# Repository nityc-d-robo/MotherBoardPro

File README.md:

This project needs some libraries in nityc-d-robo/d_robo_lib . So first, import them to Kicad5 and then, open this circuit datas.

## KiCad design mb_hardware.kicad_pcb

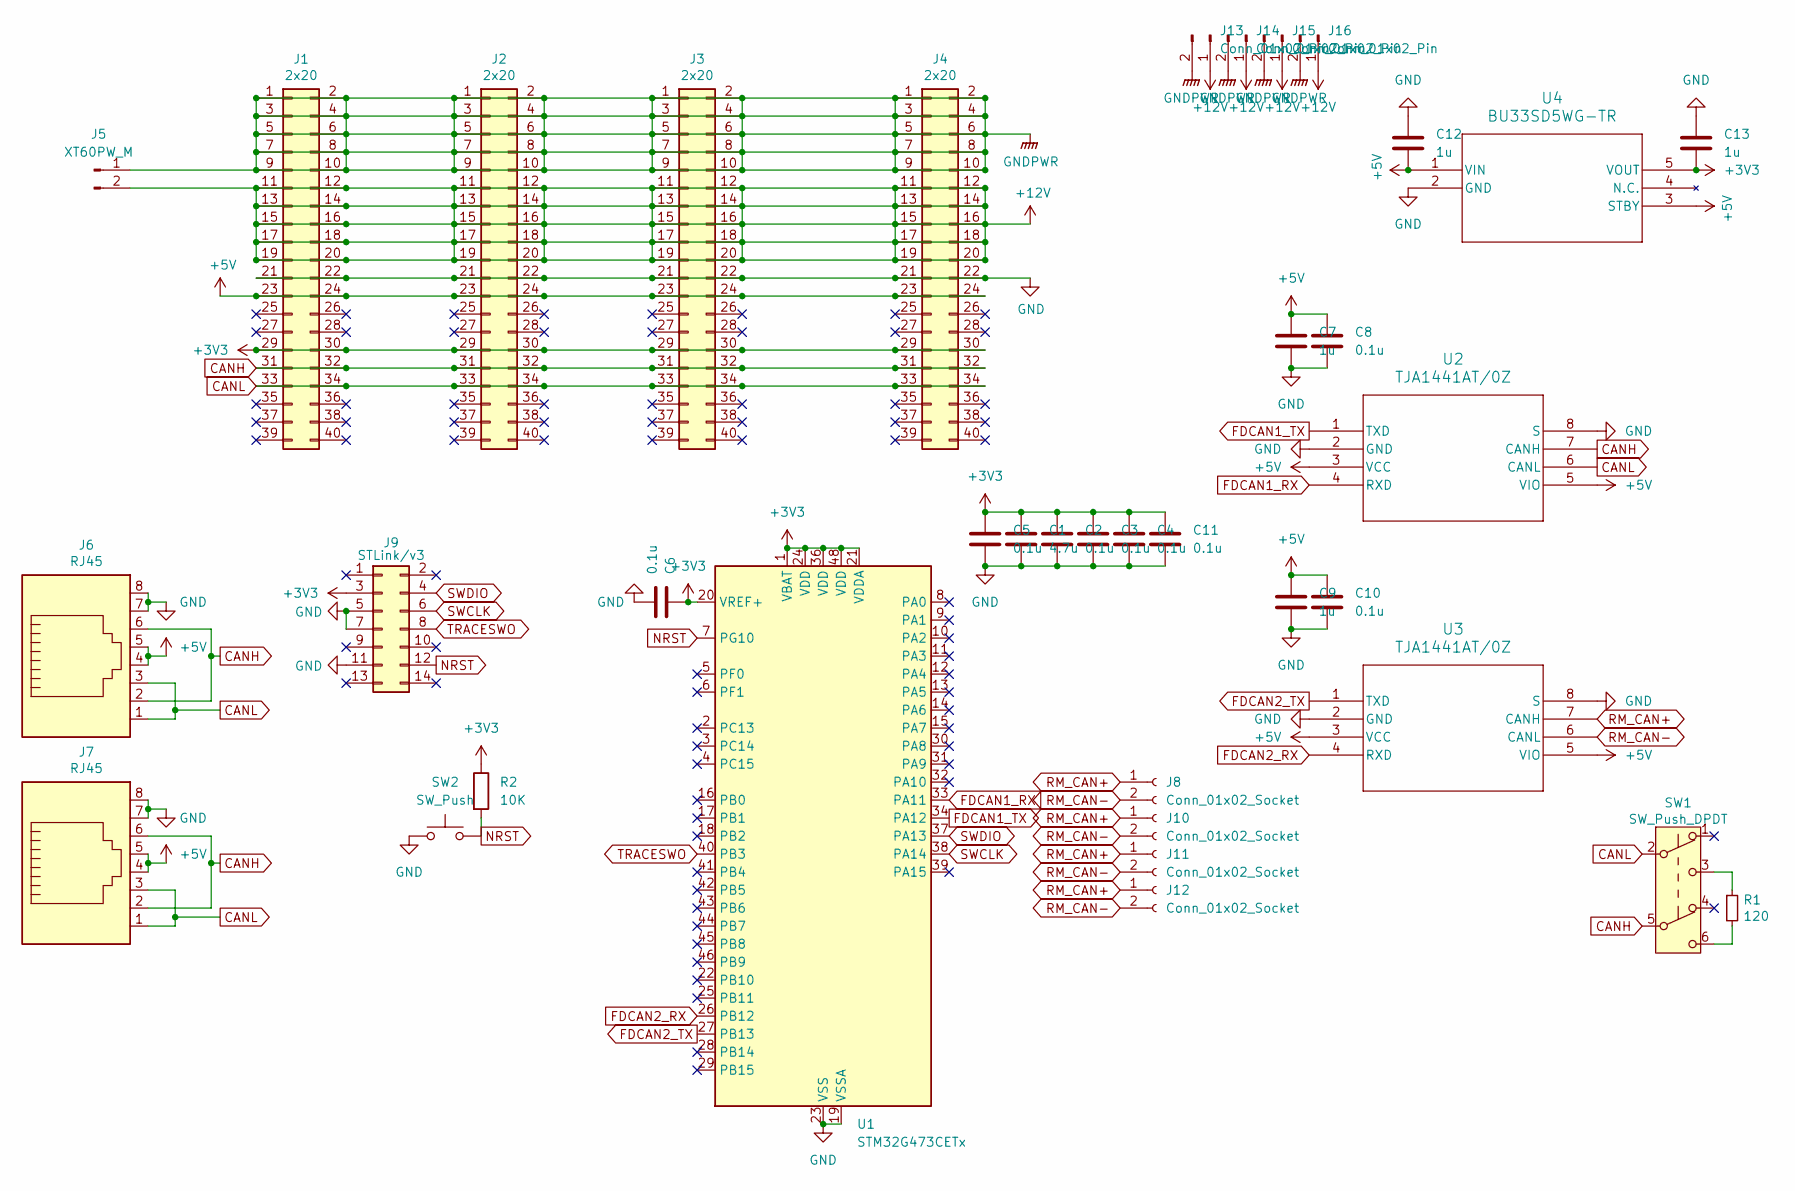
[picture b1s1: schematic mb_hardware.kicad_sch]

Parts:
C1: 4.7u; C_0603_1608Metric_Pad1.08x0.95mm_HandSolder
C2, C3, C4, C5, C6, C8, C10, C11: 0.1u; C_0603_1608Metric_Pad1.08x0.95mm_HandSolder
C7, C9, C12, C13: 1u; C_0603_1608Metric_Pad1.08x0.95mm_HandSolder
J1, J2, J3, J4: 2x20; PinSocket_2x20_P2.54mm_Vertical
J5: XT60PW_M; AMASS_XT60PW-M_1x02_P7.20mm_Horizontal
J6, J7: RJ45; RJ45_Amphenol_54602-x08_Horizontal
J8, J10, J11, J12: Conn_01x02_Socket; JST_GH_SM02B-GHS-TB_1x02-1MP_P1.25mm_Horizontal
J9: STLink/v3; CONN14_3220-14_CNC
J13, J14, J15, J16: Conn_01x02_Pin; AMASS_XT30PW-M_1x02_P2.50mm_Horizontal
R1: 120; R_0603_1608Metric_Pad0.98x0.95mm_HandSolder
R2: 10K; R_0603_1608Metric_Pad0.98x0.95mm_HandSolder
SW1: SW_Push_DPDT; SW_DPDT_CK_JS202011JCQN
SW2: SW_Push; TVAF06-A020B-R
U1: STM32G473CETx; LQFP-48_7x7mm_P0.5mm
U2, U3: TJA1441AT/0Z; SO8_SOT96-1_NXP
U4: BU33SD5WG-TR; SSOP5_ROM

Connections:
+3V3: C1.1, C2.1, C3.1, C4.1, C5.1, C6.2, C11.1, C13.1, J1.29, J1.30, J2.29, J2.30, J3.29, J3.30, J4.29, J4.30, J9.3, R2.1, U1.1 (VBAT), U1.20 (VREF+), U1.21 (VDDA), U1.24 (VDD), U1.36 (VDD), U1.48 (VDD), U4.5 (VOUT)
+5V: C7.1, C8.1, C9.1, C10.1, C12.1, J1.23, J1.24, J2.23, J2.24, J3.23, J3.24, J4.23, J4.24, J6.4, J6.5, J7.4, J7.5, U2.3 (VCC), U2.5 (VIO), U3.3 (VCC), U3.5 (VIO), U4.1 (VIN), U4.3 (STBY)
+12V: J1.11, J1.12, J1.13, J1.14, J1.15, J1.16, J1.17, J1.18, J1.19, J1.20, J2.11, J2.12, J2.13, J2.14, J2.15, J2.16, J2.17, J2.18, J2.19, J2.20, J3.11, J3.12, J3.13, J3.14, J3.15, J3.16, J3.17, J3.18, J3.19, J3.20, J4.11, J4.12, J4.13, J4.14, J4.15, J4.16, J4.17, J4.18, J4.19, J4.20, J5.2, J13.1, J14.1, J15.1, J16.1
CANH: J1.31, J1.32, J2.31, J2.32, J3.31, J3.32, J4.31, J4.32, J6.2, J6.6, J7.2, J7.6, SW1.5 (B), U2.7 (CANH)
CANL: J1.33, J1.34, J2.33, J2.34, J3.33, J3.34, J4.33, J4.34, J6.1, J6.3, J7.1, J7.3, SW1.2 (B), U2.6 (CANL)
FDCAN1_RX: U1.33 (PA11), U2.4 (RXD)
FDCAN1_TX: U1.34 (PA12), U2.1 (TXD)
FDCAN2_RX: U1.26 (PB12), U3.4 (RXD)
FDCAN2_TX: U1.27 (PB13), U3.1 (TXD)
GND: C1.2, C2.2, C3.2, C4.2, C5.2, C6.1, C7.2, C8.2, C9.2, C10.2, C11.2, C12.2, C13.2, J1.21, J1.22, J2.21, J2.22, J3.21, J3.22, J4.21, J4.22, J6.7, J6.8, J7.7, J7.8, J9.5, J9.7, J9.11, SW2.1, U1.19 (VSSA), U1.23 (VSS), U1.35 (VSS), U1.47 (VSS), U2.2 (GND), U2.8 (S), U3.2 (GND), U3.8 (S), U4.2 (GND)
GNDPWR: J1.1, J1.2, J1.3, J1.4, J1.5, J1.6, J1.7, J1.8, J1.9, J1.10, J2.1, J2.2, J2.3, J2.4, J2.5, J2.6, J2.7, J2.8, J2.9, J2.10, J3.1, J3.2, J3.3, J3.4, J3.5, J3.6, J3.7, J3.8, J3.9, J3.10, J4.1, J4.2, J4.3, J4.4, J4.5, J4.6, J4.7, J4.8, J4.9, J4.10, J5.1, J13.2, J14.2, J15.2, J16.2
NRST: J9.12, R2.2, SW2.2, U1.7 (PG10)
unnamed: R1.1, SW1.3 (C)
unnamed: R1.2, SW1.6 (C)
RM_CAN+: J8.1, J10.1, J11.1, J12.1, U3.7 (CANH)
RM_CAN-: J8.2, J10.2, J11.2, J12.2, U3.6 (CANL)
SWCLK: J9.6, U1.38 (PA14)
SWDIO: J9.4, U1.37 (PA13)
TRACESWO: J9.8, U1.40 (PB3)

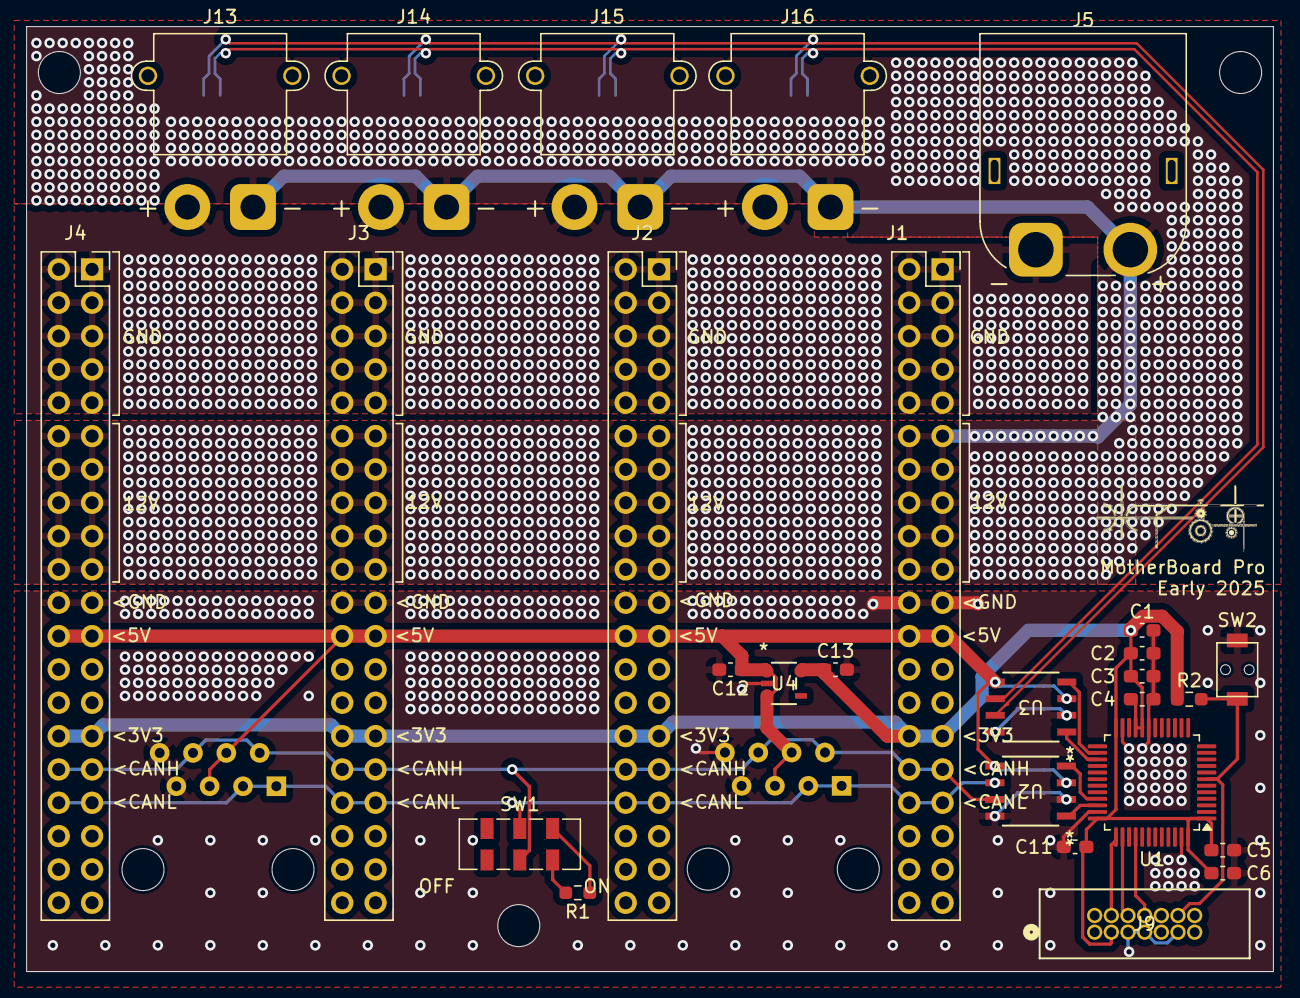
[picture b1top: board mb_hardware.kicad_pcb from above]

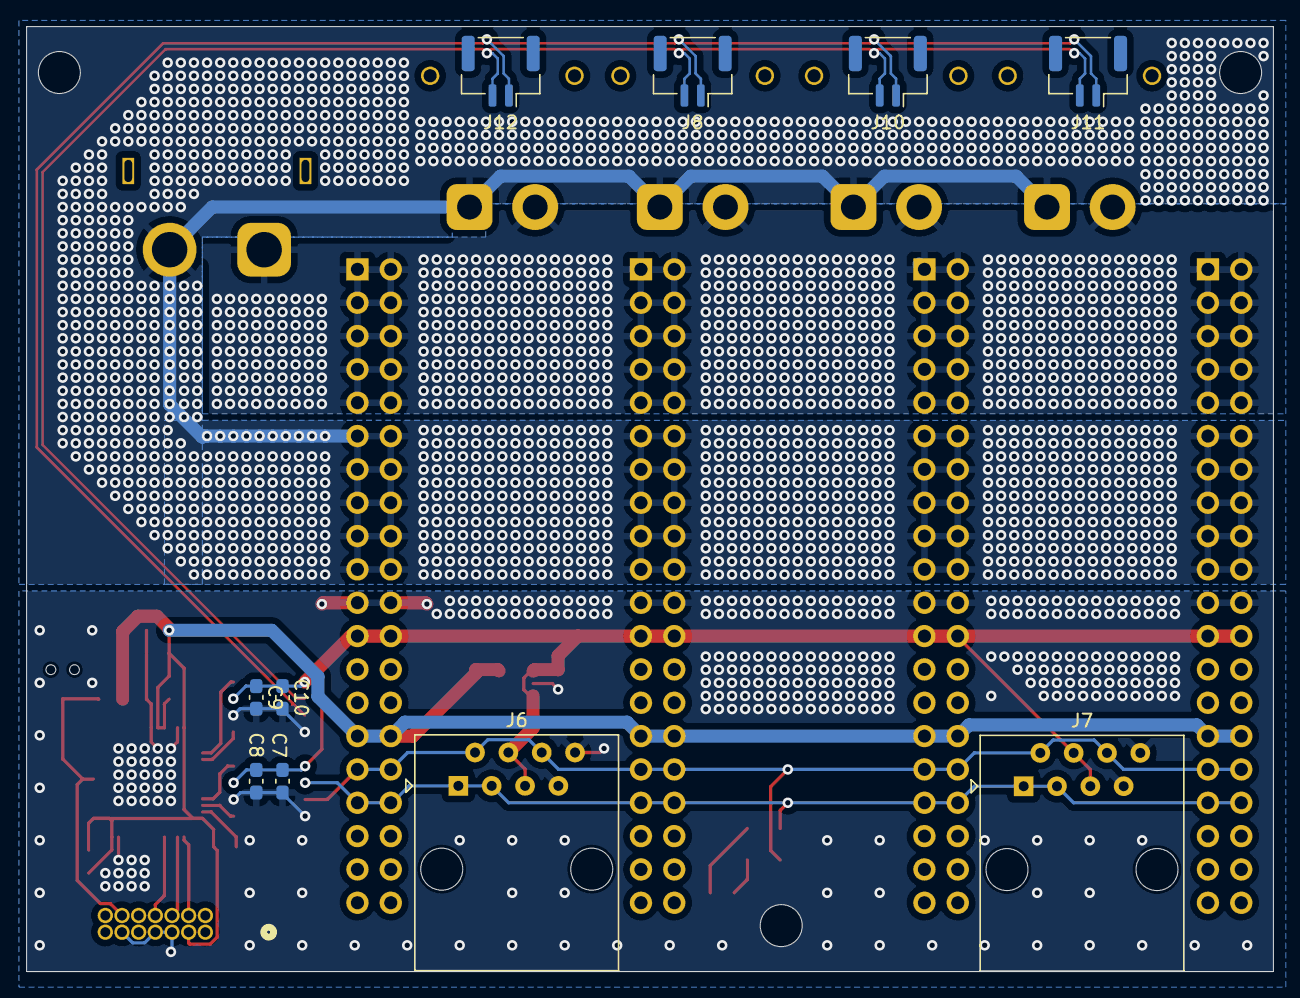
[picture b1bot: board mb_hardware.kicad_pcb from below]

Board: 2 copper layers, 95.0 x 72.0 mm, 37 parts (10 on the bottom side), 19 nets.

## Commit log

2025-04-27 All New Camera.
2025-04-27 Lightweight Performance.
